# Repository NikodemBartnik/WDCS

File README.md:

# WDCS
Watering and Data Collection System based on Arduino and a lot of sensors

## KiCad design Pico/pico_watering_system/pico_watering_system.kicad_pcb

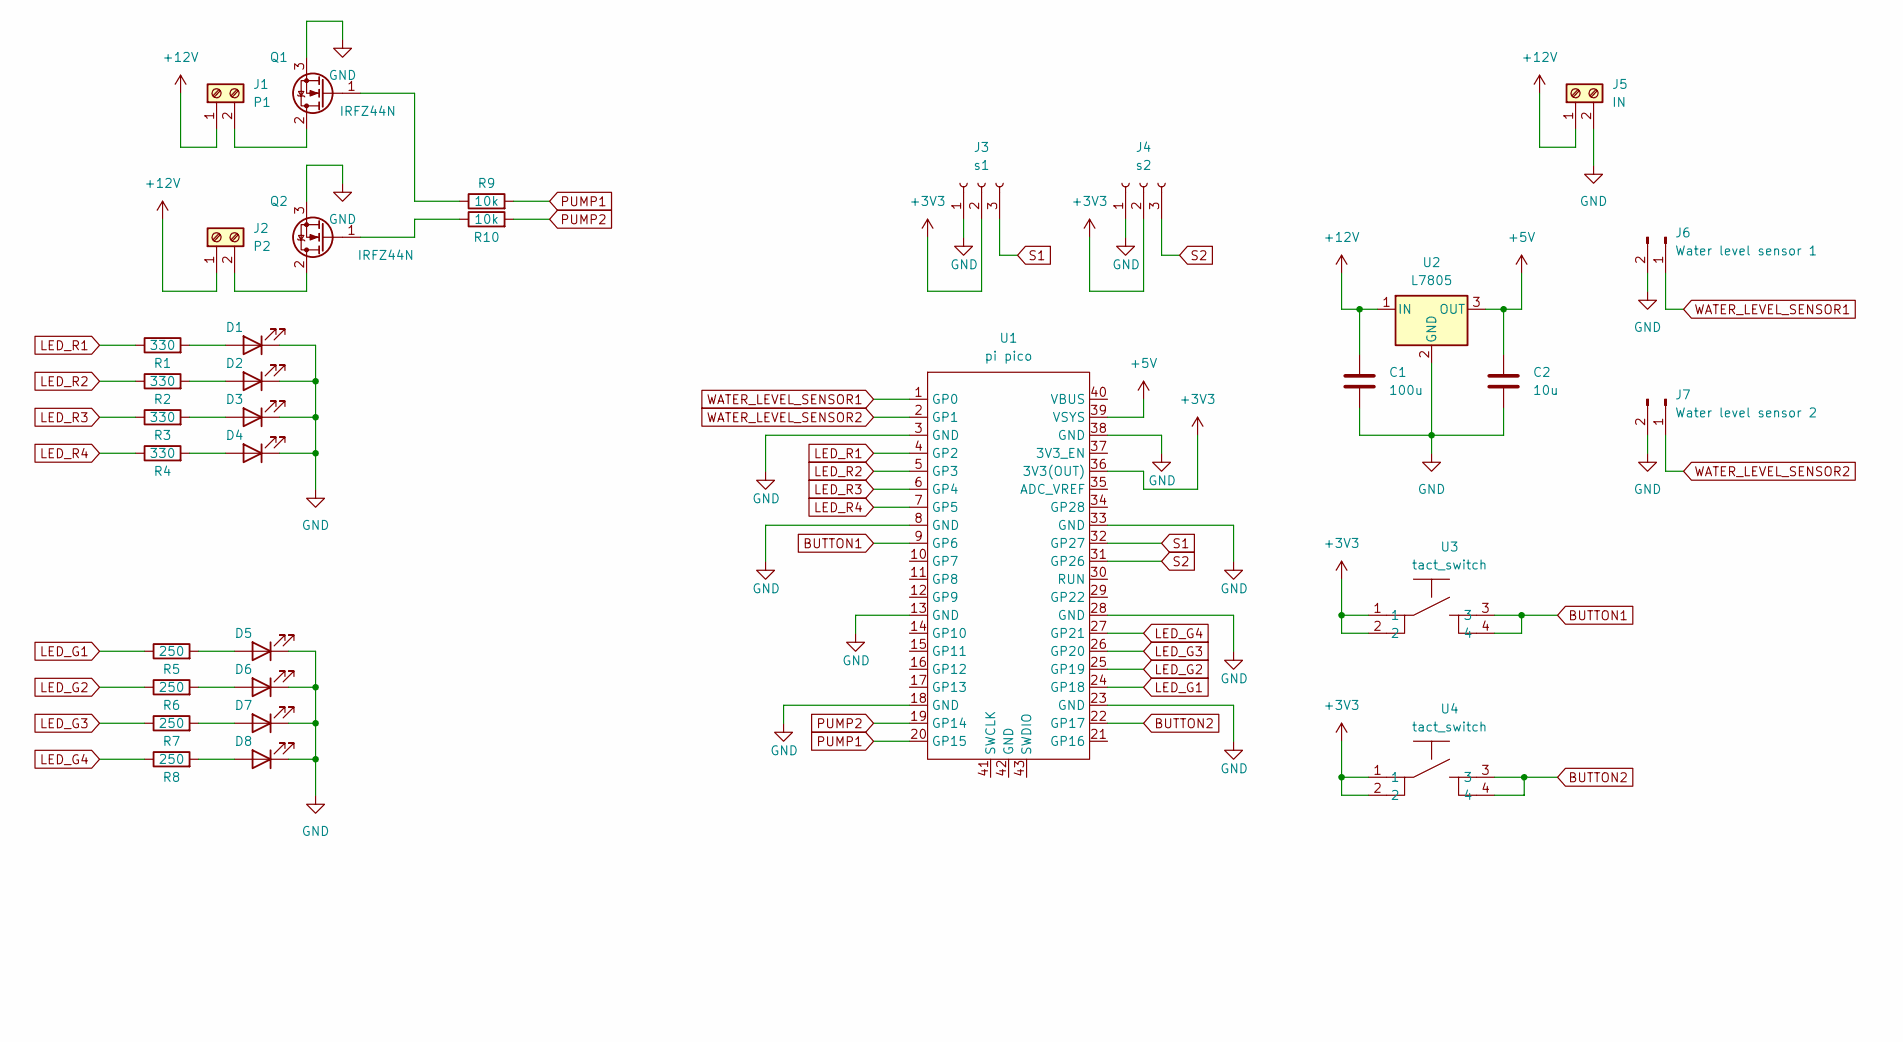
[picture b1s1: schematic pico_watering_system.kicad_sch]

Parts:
C1: 100u; C_Disc_D3.0mm_W2.0mm_P2.50mm
C2: 10u; C_Disc_D3.0mm_W2.0mm_P2.50mm
D1, D2, D3, D4, D5, D6, D7, D8: LED; LED_D5.0mm
J1: P1; TerminalBlock_Phoenix_MKDS-1,5-2-5.08_1x02_P5.08mm_Horizont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
J2: P2; TerminalBlock_Phoenix_MKDS-1,5-2-5.08_1x02_P5.08mm_Horizont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
J3: s1; PinSocket_1x03_P2.54mm_Vertical
J4: s2; PinSocket_1x03_P2.54mm_Vertical
J5: IN; TerminalBlock_Phoenix_MKDS-1,5-2-5.08_1x02_P5.08mm_Horizont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
J6: Water level sensor 1; PinHeader_1x02_P2.54mm_Vertical
J7: Water level sensor 2; PinHeader_1x02_P2.54mm_Vertical
Q1, Q2: IRFZ44N; TO-220-3_Vertical
R1, R2, R3, R4: 330; R_1206_3216Metric_Pad1.30x1.75mm_HandSolder
R5, R6, R7, R8: 250; R_1206_3216Metric_Pad1.30x1.75mm_HandSolder
R9, R10: 10k; R_1206_3216Metric_Pad1.30x1.75mm_HandSolder
U1: pi pico; raspberry pi pico
U2: L7805; TO-220-3_Vertical
U3, U4: tact_switch

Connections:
+3V3: J3.2, J4.2, U1.36 (3V3(OUT)), U3.1, U3.2, U4.1, U4.2
+5V: C2.1, U1.39 (VSYS), U2.3 (OUT)
+12V: C1.1, J1.1, J2.1, J5.1, U2.1 (IN)
BUTTON1: U1.9 (GP6), U3.3, U3.4
BUTTON2: U1.22 (GP17), U4.3, U4.4
GND: C1.2, C2.2, D1.1 (K), D2.1 (K), D3.1 (K), D4.1 (K), D5.1 (K), D6.1 (K), D7.1 (K), D8.1 (K), J3.1, J4.1, J5.2, J6.2, J7.2, Q1.3 (S), Q2.3 (S), U1.3 (GND), U1.8 (GND), U1.13 (GND), U1.18 (GND), U1.23 (GND), U1.28 (GND), U1.33 (GND), U1.38 (GND), U2.2 (GND)
LED_G1: R5.1, U1.24 (GP18)
LED_G2: R6.1, U1.25 (GP19)
LED_G3: R7.1, U1.26 (GP20)
LED_G4: R8.1, U1.27 (GP21)
LED_R1: R1.1, U1.4 (GP2)
LED_R2: R2.1, U1.5 (GP3)
LED_R3: R3.1, U1.6 (GP4)
LED_R4: R4.1, U1.7 (GP5)
unnamed: D1.2 (A), R1.2
unnamed: D2.2 (A), R2.2
unnamed: D3.2 (A), R3.2
unnamed: D4.2 (A), R4.2
unnamed: D5.2 (A), R5.2
unnamed: D6.2 (A), R6.2
unnamed: D7.2 (A), R7.2
unnamed: D8.2 (A), R8.2
unnamed: J1.2, Q1.2 (D)
unnamed: J2.2, Q2.2 (D)
unnamed: Q1.1 (G), R9.1
unnamed: Q2.1 (G), R10.1
PUMP1: R9.2, U1.20 (GP15)
PUMP2: R10.2, U1.19 (GP14)
S1: J3.3, U1.32 (GP27)
S2: J4.3, U1.31 (GP26)
WATER_LEVEL_SENSOR1: J6.1, U1.1 (GP0)
WATER_LEVEL_SENSOR2: J7.1, U1.2 (GP1)

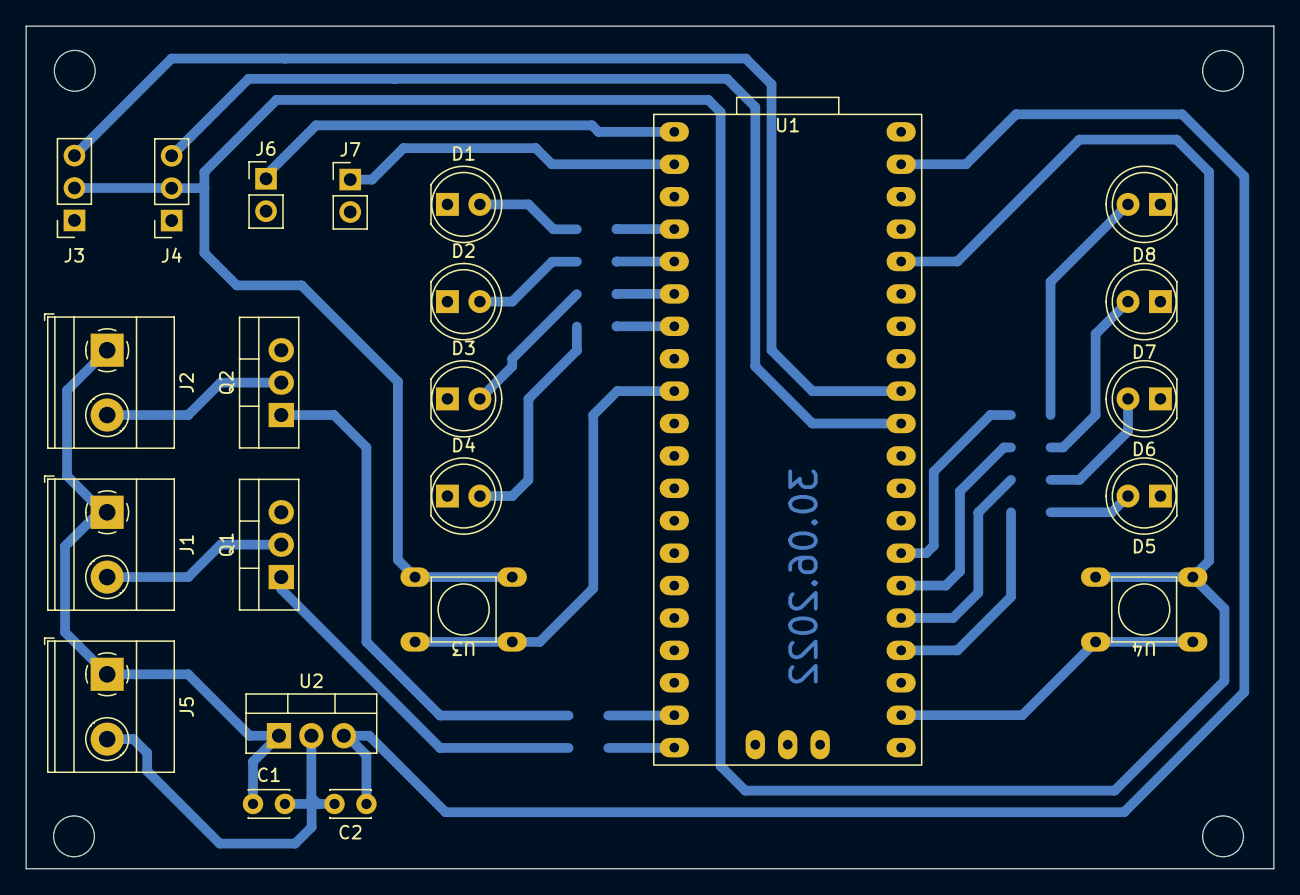
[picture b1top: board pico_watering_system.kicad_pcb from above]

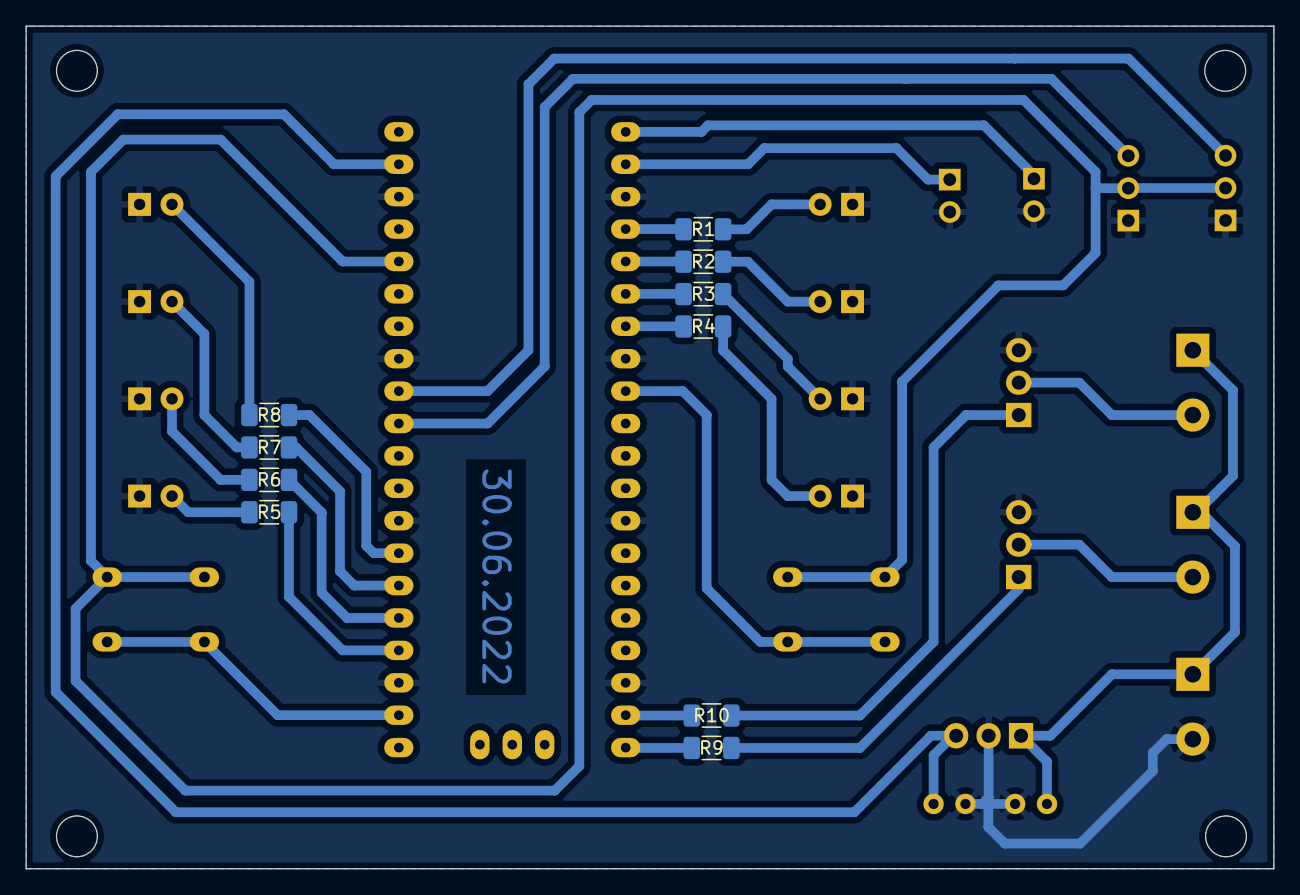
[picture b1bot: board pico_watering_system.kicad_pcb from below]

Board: 2 copper layers, 97.8 x 66.0 mm, 33 parts (10 on the bottom side), 32 nets.

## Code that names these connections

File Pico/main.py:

from machine import Pin, ADC, Timer
import time, os

#constants
PIN_PUMP_1 = 15
PIN_PUMP_2 = 14
PIN_LED_R_1 = 2
PIN_LED_R_2 = 3
PIN_LED_R_3 = 4
PIN_LED_R_4 = 5
PIN_LED_G_1 = 18
PIN_LED_G_2 = 19
PIN_LED_G_3 = 20
PIN_LED_G_4 = 21

PIN_BUTTON_1 = 6
PIN_BUTTON_2 = 17

PIN_WATER_LEVEL_SENSOR_1 = 0
PIN_WATER_LEVEL_SENSOR_2 = 1

WATERING_CYCLE_TIMES_ARRAY = [2, 4, 6, 8] #time in minutes

#global variables
selectionActive = True
dailyWateringCycles = 3 
wateringCycleTime = 1 #choose from WATERING_CYCLE_TIMES
selectionTimer = Timer()
lastWatering = time.time()

pump1 = Pin(PIN_PUMP_1, Pin.OUT)
pump2 = Pin(PIN_PUMP_2, Pin.OUT)

ledR1 = Pin(PIN_LED_R_1, Pin.OUT)
ledR2 = Pin(PIN_LED_R_2, Pin.OUT)
ledR3 = Pin(PIN_LED_R_3, Pin.OUT)
ledR4 = Pin(PIN_LED_R_4, Pin.OUT)
ledG1 = Pin(PIN_LED_G_1, Pin.OUT)
ledG2 = Pin(PIN_LED_G_2, Pin.OUT)
ledG3 = Pin(PIN_LED_G_3, Pin.OUT)
ledG4 = Pin(PIN_LED_G_4, Pin.OUT)

button1 = Pin(PIN_BUTTON_1, Pin.IN, Pin.PULL_DOWN)
button2 = Pin(PIN_BUTTON_2, Pin.IN, Pin.PULL_DOWN)
wl1 = Pin(PIN_WATER_LEVEL_SENSOR_1, Pin.IN, Pin.PULL_UP)
wl2 = Pin(PIN_WATER_LEVEL_SENSOR_2, Pin.IN, Pin.PULL_UP)


def checkKeys():
    global selectionActive
    if(button1.value() or button2.value()):
        selectionActive = True
        selectionTimer.init(mode=Timer.ONE_SHOT, period=10000, callback=disableSelection)
        
def disableSelection(t):
    global selectionActive
    selectionActive = False
    ledR1.value(0)
    ledR2.value(0)
    ledR3.value(0)
    ledR4.value(0)
    ledG1.value(0)
    ledG2.value(0)
    ledG3.value(0)
    ledG4.value(0)
    saveSettings()
    selectionTimer.init(mode=Timer.PERIODIC, freq=0.1, callback=signOfLife)
    
    
def saveSettings():
    #saving settings
    try:
        os.remove('t.txt')
    except OSError:
        print("t.txt doesn't exists")
    try:
        os.remove('c.txt')
    except OSError:
        print("t.txt doesn't exists")
        
    f = open('t.txt', 'w+')
    f.write(str(wateringCycleTime))
    f.close()
    f = open('c.txt', 'w+')
    f.write(str(dailyWateringCycles))
    f.close()
    
def loadSettings():
    global wateringCycleTime, dailyWateringCycles
    try:
        f = open('t.txt')
        wateringCycleTime = int(f.read())
        print('wateringCycleTime', wateringCycleTime)
        f.close()
    except OSError:
        print("t.txt doesn't exists")
    try: 
        f = open('c.txt')
        dailyWateringCycles = int(f.read())
        print('dailyWateringCycles', dailyWateringCycles)
        f.close()
    except OSError:
        print("c.txt doesn't exists")

    
def displayWateringTimes():
    if(selectionActive):
        ledR4.value(1) if wateringCycleTime >= 0 else ledR4.value(0)
        ledR3.value(1) if wateringCycleTime >= 1 else ledR3.value(0)
        ledR2.value(1) if wateringCycleTime >= 2 else ledR2.value(0)
        ledR1.value(1) if wateringCycleTime >= 3 else ledR1.value(0)
        
        
def displayWateringCycles():
    if(selectionActive):
        ledG1.value(1) if dailyWateringCycles >= 0 else ledG1.value(0)
        ledG2.value(1) if dailyWateringCycles >= 1 else ledG2.value(0)
        ledG3.value(1) if dailyWateringCycles >= 2 else ledG3.value(0)
        ledG4.value(1) if dailyWateringCycles >= 3 else ledG4.value(0)
    

def checkAndModifySettings():
    global wateringCycleTime, dailyWateringCycles
    if(button1.value()):
        time.sleep_ms(50)
        if(button1.value()):
            wateringCycleTime = (wateringCycleTime+1) if wateringCycleTime < 3 else 0
            displayWateringTimes()
            time.sleep_ms(200)
    
    if(button2.value()):
        time.sleep_ms(50)
        if(button2.value()):
            dailyWateringCycles = (dailyWateringCycles+1) if dailyWateringCycles < 3 else 0
            displayWateringCycles()
            time.sleep_ms(200)
            
            

def checkWatering():
    global lastWatering
    if((time.time() - lastWatering) > (86400/(dailyWateringCycles + 1))):
        wateringStart = time.time()
        if(checkWaterLevel()):
        pump1.value(1)
            while(time.time() - wateringStart < (WATERING_CYCLE_TIMES_ARRAY[wateringCycleTime]*60)):
                ledG1.value(1)
                time.sleep_ms(200)
                ledG1.value(0)
                time.sleep_ms(200)
            pump1.value(0)
        lastWatering = time.time()
        
        
def signOfLife(t):
    ledR1.value(1)
    time.sleep_ms(10)
    ledR1.value(0)
    print('sign of life')
    
def checkWaterLevel():
    return 0 if wl1.value() else 1
    

#loading the settings from flash before entering the loop
loadSettings()
#disable LEDs after 10 seconds
selectionTimer.init(mode=Timer.ONE_SHOT, period=10000, callback=disableSelection)

while(1):
    checkKeys()
    checkWatering()
    if(selectionActive):
        checkAndModifySettings()
        displayWateringTimes()
        displayWateringCycles()
    time.sleep_ms(50)

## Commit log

2022-06-23 code update
2022-06-24 Add min and max no watering time, cleanup
2022-06-30 after milling
2022-07-04 menu and storing data finished
2022-07-04 final v1
2022-07-05 water level check, proper 24h in seconds
2022-07-05 add case
2022-07-11 Add no water alarm
2022-07-12 Added STL files, data files and cleanup
